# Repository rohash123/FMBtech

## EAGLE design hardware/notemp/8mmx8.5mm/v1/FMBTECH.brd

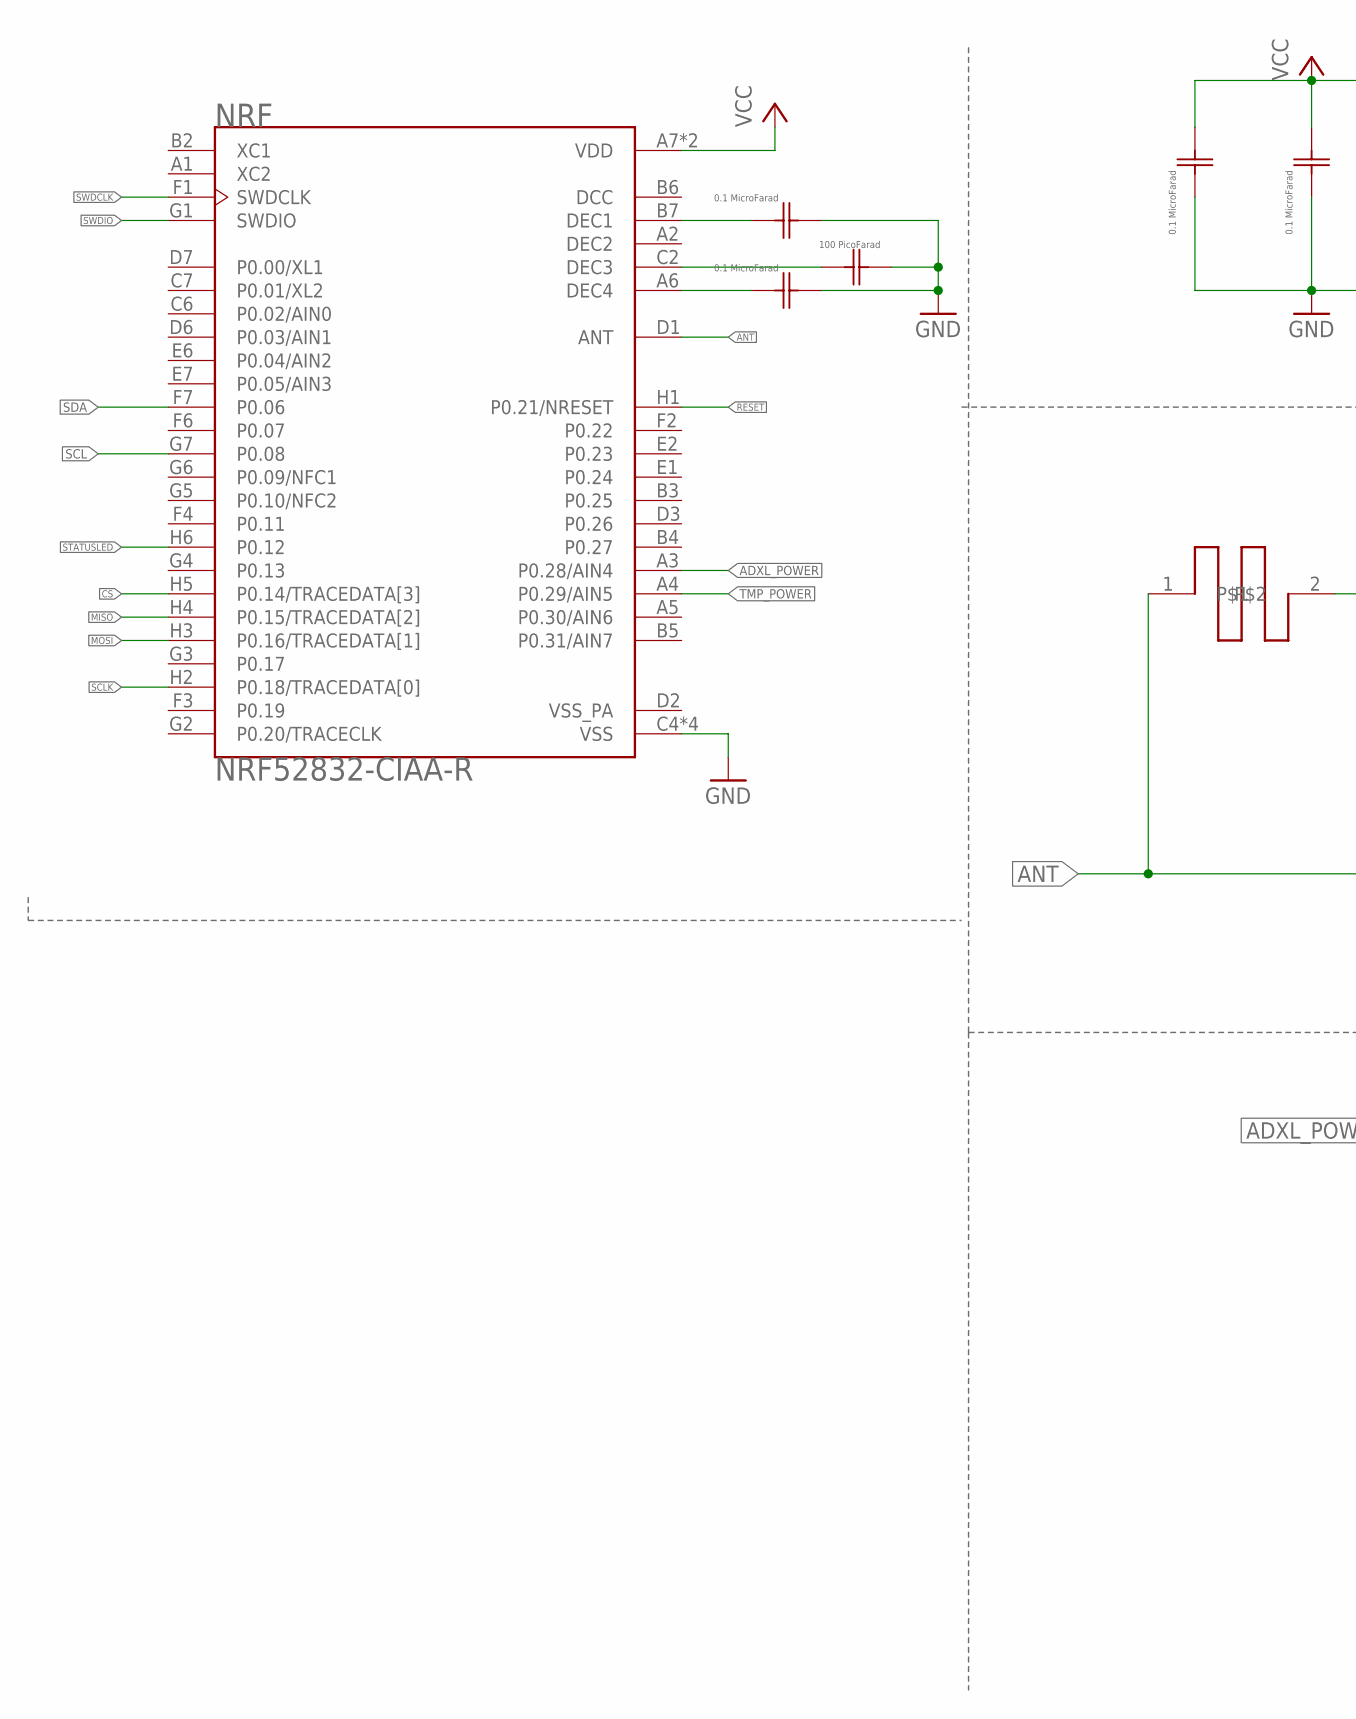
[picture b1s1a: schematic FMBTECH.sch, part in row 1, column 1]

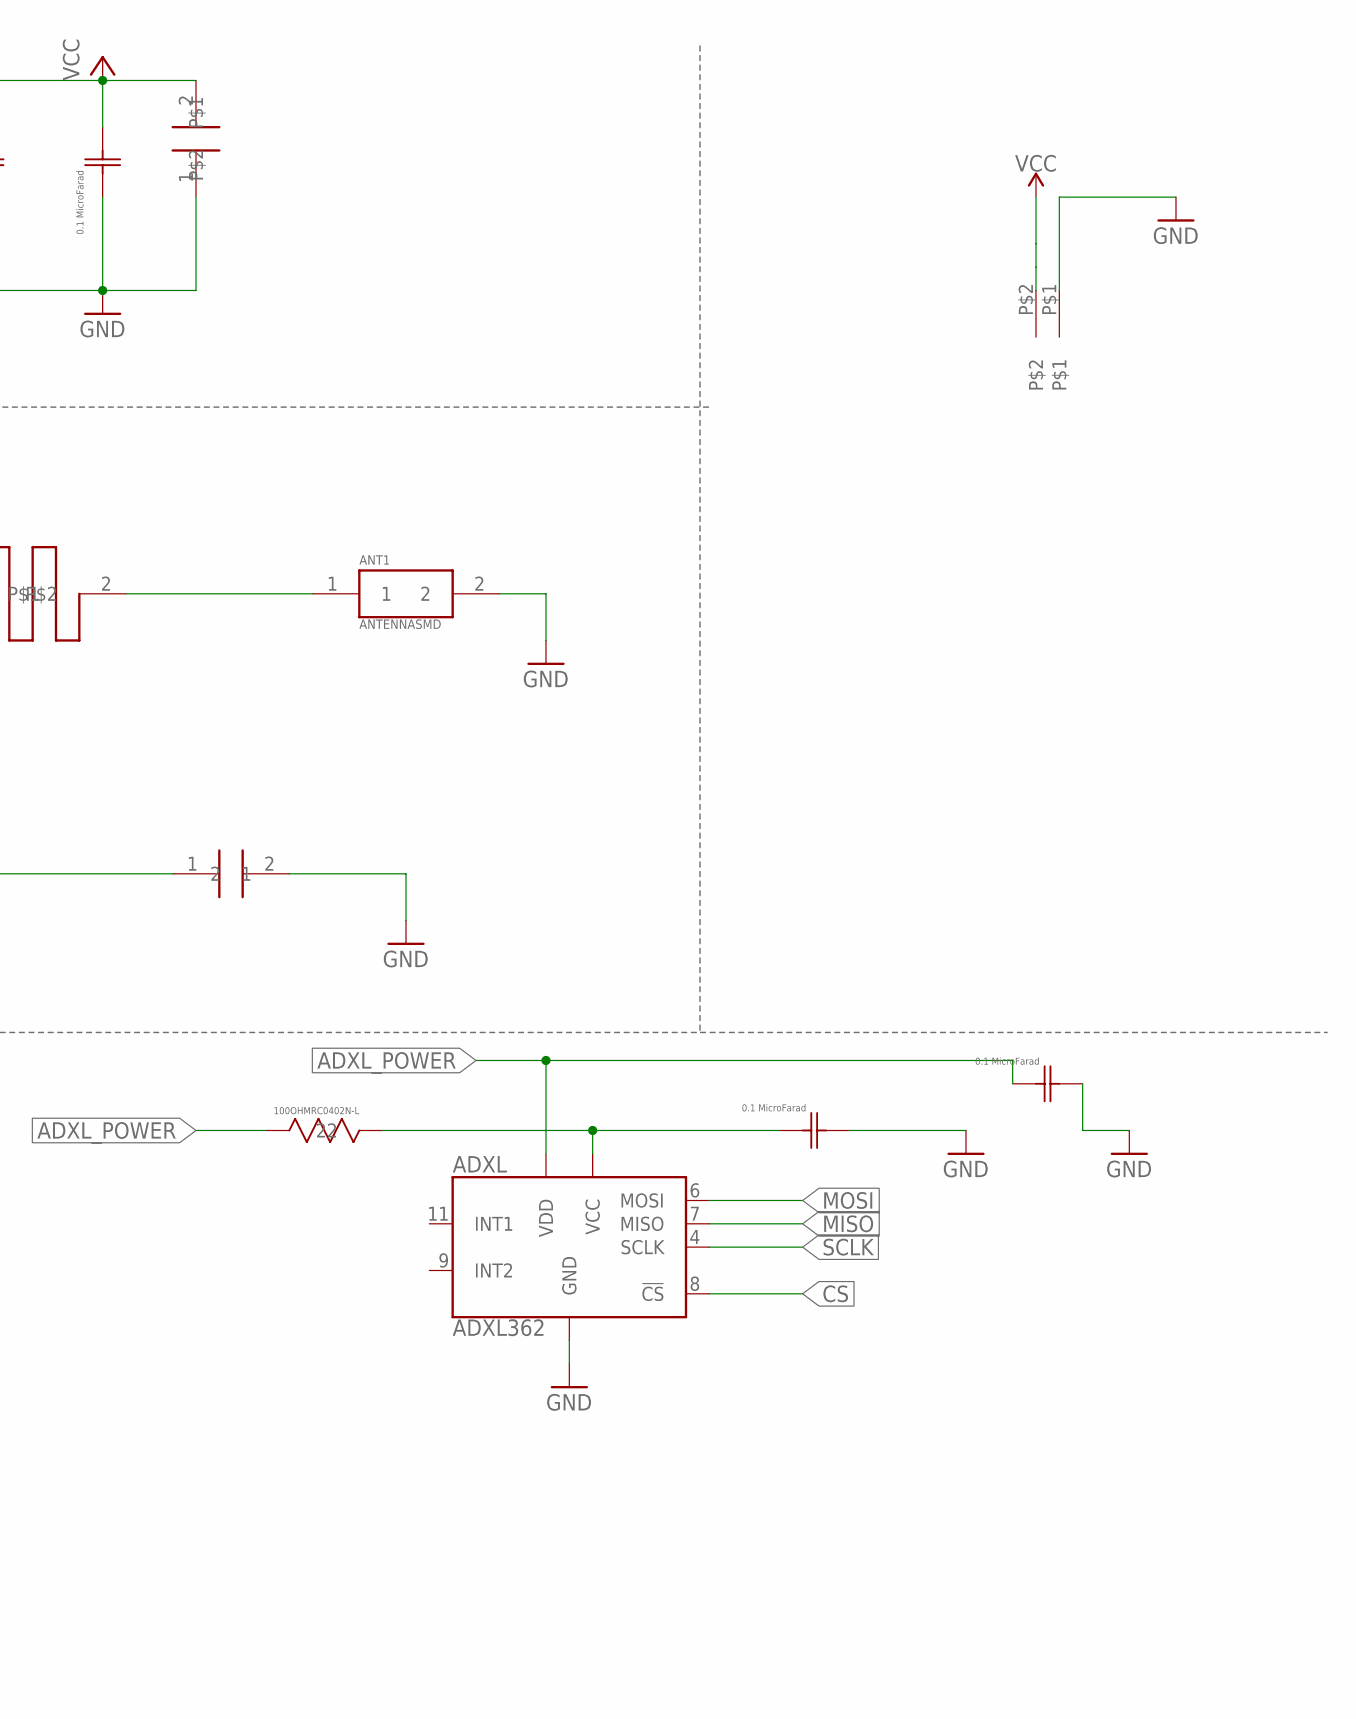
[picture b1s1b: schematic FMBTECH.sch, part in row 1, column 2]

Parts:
ADXL: ADXL362; TFLGA-16/3.3MMX3.1MM
ANT1: ANTENNASMD; 1
C1, C2, C6, C7, C8, C9: 02016D104KAT2A; 0201
C3: GRM0335C1E101JA01D; G-033
NRF: NRF52832-CIAA-R; BGA50N40P7X8_300X320X40
R6: 100OHMRC0402N-L; RES
U$1: 4.7µF; CAP
U$2: 0.8PF; CAP
U$3: INDUCTOR; 1
U$4: SUPPLY

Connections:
ADXL_POWER: ADXL.1 (VDD), C9.1, NRF.A3 (P0.28/AIN4), R6.1 (11)
ANT: NRF.D1 (ANT), U$2.1, U$3.1
CS: ADXL.8 (!CS), NRF.H5 (P0.14/TRACEDATA[3])
DCC: NRF.B6 (DCC)
DEC2: NRF.A2 (DEC2)
GND: ADXL.12 (GND), ADXL.13 (GND), ADXL.16 (GND), ANT1.2, C1.2, C2.2, C3.2 (22), C6.1, C7.1, C8.2, C9.2, NRF.C4 (VSS), NRF.C5 (VSS), NRF.E3 (VSS), NRF.F5 (VSS), U$1.1, U$2.2, U$4.P$1
MISO: ADXL.7 (MISO), NRF.H4 (P0.15/TRACEDATA[2])
MOSI: ADXL.6 (MOSI), NRF.H3 (P0.16/TRACEDATA[1])
unnamed: ANT1.1, U$3.2
unnamed: C2.1, NRF.A6 (DEC4)
unnamed: C1.1, NRF.B7 (DEC1)
unnamed: C3.1 (11), NRF.C2 (DEC3)
unnamed: ADXL.14 (VCC), C8.1, R6.2 (22)
RESET: NRF.H1 (P0.21/NRESET)
SCL: NRF.G7 (P0.08)
SCLK: ADXL.4 (SCLK), NRF.H2 (P0.18/TRACEDATA[0])
SDA: NRF.F7 (P0.06)
STATUSLED: NRF.H6 (P0.12)
SWDCLK: NRF.F1 (SWDCLK)
SWDIO: NRF.G1 (SWDIO)
TMP_POWER: NRF.A4 (P0.29/AIN5)
VCC: C6.2, C7.2, NRF.A7 (VDD), NRF.H7 (VDD), U$1.2, U$4.P$2
VSS_PA: NRF.D2 (VSS_PA)

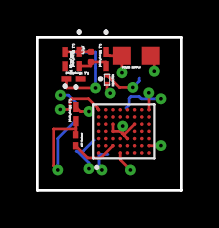
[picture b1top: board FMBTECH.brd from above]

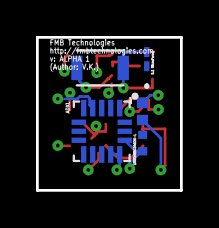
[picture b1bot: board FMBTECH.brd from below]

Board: 6 copper layers, 8.0 x 8.5 mm, 15 parts (5 on the bottom side), 13 nets.

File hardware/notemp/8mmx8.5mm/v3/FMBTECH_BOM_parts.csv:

"Part";"Value";"Device";"Package";"Description";"";
"ADXL";"ADXL362";"ADXL362";"TFLGA-16/3.3MMX3.1MM";"IC ACCEL DIG LO PWR 3AX 16LGA";"";
"ANT1";"ANTENNASMD";"ANTENNASMD";"1";"";"";
"C1";"02016D104KAT2A";"02016D104KAT2A";"0201";"";"";
"C2";"02016D104KAT2A";"02016D104KAT2A";"0201";"";"";
"C3";"GRM0335C1E101JA01D";"GRM0335C1E101JA01D";"G-033";"";"";
"C6";"02016D104KAT2A";"02016D104KAT2A";"0201";"";"";
"C7";"02016D104KAT2A";"02016D104KAT2A";"0201";"";"";
"C8";"02016D104KAT2A";"02016D104KAT2A";"0201";"";"";
"C9";"02016D104KAT2A";"02016D104KAT2A";"0201";"";"";
"NRF";"NRF52832-CIAA-R";"NRF52832-CIAA-R";"BGA50N40P7X8_300X320X40";"Multi Protocal Bluetooth Smart ANT 2.4GHz RF SoC (WL-CSP)";"";
"R6";"100OHMRC0402N-L";"100OHMRC0402N-L";"RES";"";"";
"U$1";"4.7µF";"4.7µF";"CAP";"";"";
"U$2";"0.8PF";"0.8PF";"CAP";"";"";
"U$3";"INDUCTOR";"INDUCTOR";"1";"";"";
"U$4";"SUPPLY";"SUPPLY";"SUPPLY";"";"";

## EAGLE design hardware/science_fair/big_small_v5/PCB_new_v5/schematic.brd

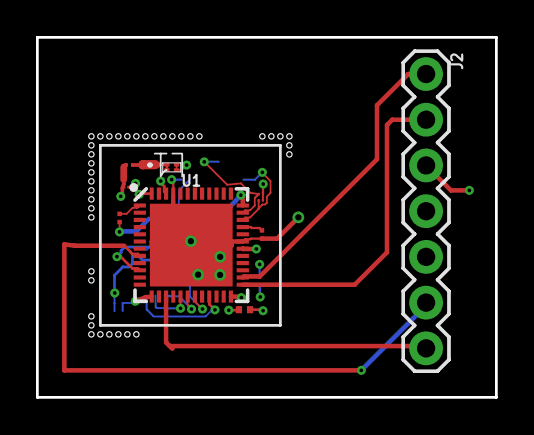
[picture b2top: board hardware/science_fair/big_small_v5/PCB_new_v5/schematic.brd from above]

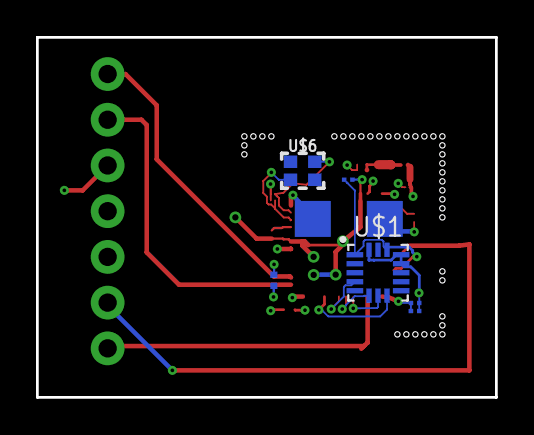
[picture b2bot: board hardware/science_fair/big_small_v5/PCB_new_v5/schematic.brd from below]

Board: 6 copper layers, 25.5 x 20.0 mm, 17 parts (7 on the bottom side), 19 nets.

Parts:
C1, C2, C3, C4: C0402X5R0G104M020BCCAP_0402-L; CAP_0402-L
C5: C0402C0G1C101J020BCCAP_0402-L; CAP_0402-L
J2: header; 1X07
L1: MLG0402Q3N9ST000IND_0402-L; IND_0402-L
U1: NRF52832; QFN48-6X6MM
U$1: ADXL362; TFLGA-16/3.3MMX3.1MM
U$2: 4P7UFCAPACITOR
U$4: 0P8PFCAPACITOR
U$5: ANTENNA; ANTENNA_FOOTPRINT
U$6: 32MHZCRYSTAL
U$7: 1UFCAPACITOR
U$8, U$9: 6PFCAPACITOR
U$10: POWER

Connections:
ADXL_POWER-QFAA: C1.2, U1.10, U$1.VDD/IO, U$1.VS
ANT-QFAA: L1.2, U1.30, U$4.P$2
CS-QFAA: U1.21, U$1.CS
DEC1-QFAA: C2.1, U1.1
DEC3-QFAA: C5.1, U1.33
DEC4-QFAA: U1.46, U$7.P$4
GND: C1.1, C2.2, C3.1, C4.1, C5.2, J2.4, U1.31, U1.45, U1.EP, U$1.GND@1, U$1.GND@2, U$1.GND@3, U$2.P$4, U$4.P$1, U$5.GND@1, U$5.GND@2, U$7.P$3, U$8.P$1, U$9.P$1, U$10.GND
MISO-QFAA: U1.17, U$1.MISO
MOSI-QFAA: U1.18, U$1.MOSI
unnamed: L1.1, U$5.FEED@1, U$5.FEED@2
P0.06-QFAA: J2.6, U1.8
P0.12-QFAA: J2.7, U1.15
RESET-QFAA: J2.5, U1.24
SCLK-QFAA: U1.19, U$1.SCLK
SWDCLK-QFAA: J2.2, U1.25
SWDIO-QFAA: J2.1, U1.26
VDD: C3.2, C4.2, J2.3, U1.13, U1.36, U1.48, U$2.P$3, U$10.VDD
XC1-QFAA: U1.34, U$6.1, U$8.P$2
XC2-QFAA: U1.35, U$6.3, U$9.P$2

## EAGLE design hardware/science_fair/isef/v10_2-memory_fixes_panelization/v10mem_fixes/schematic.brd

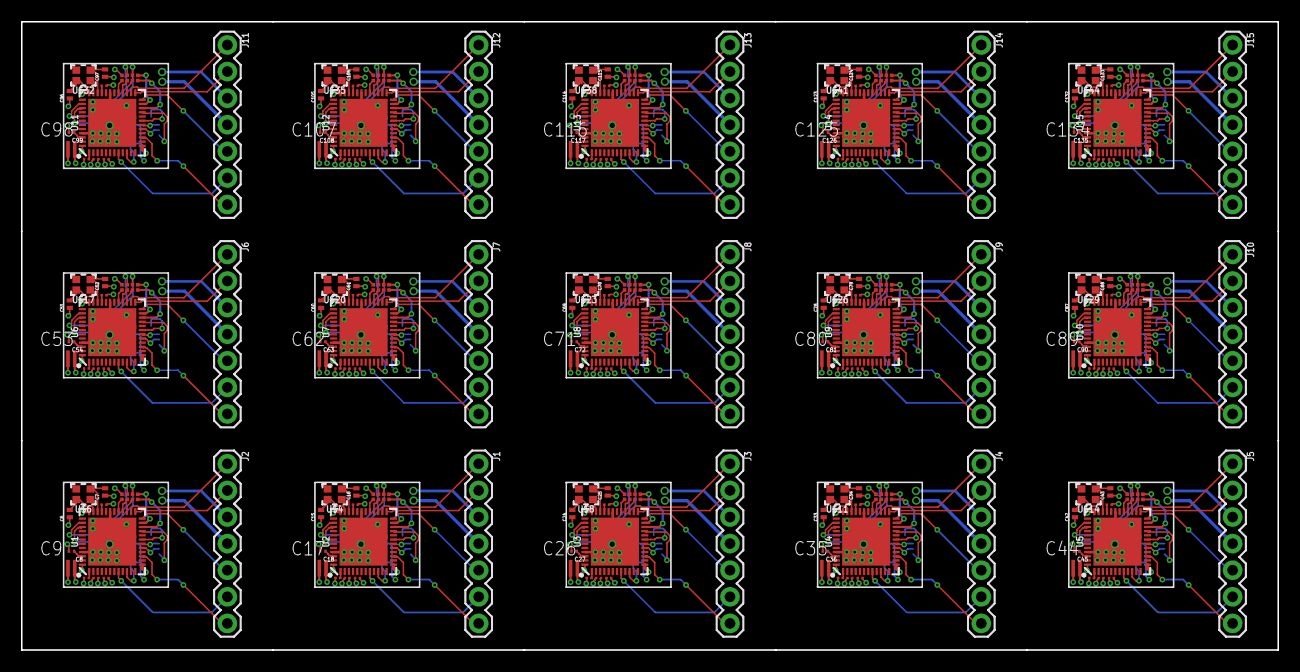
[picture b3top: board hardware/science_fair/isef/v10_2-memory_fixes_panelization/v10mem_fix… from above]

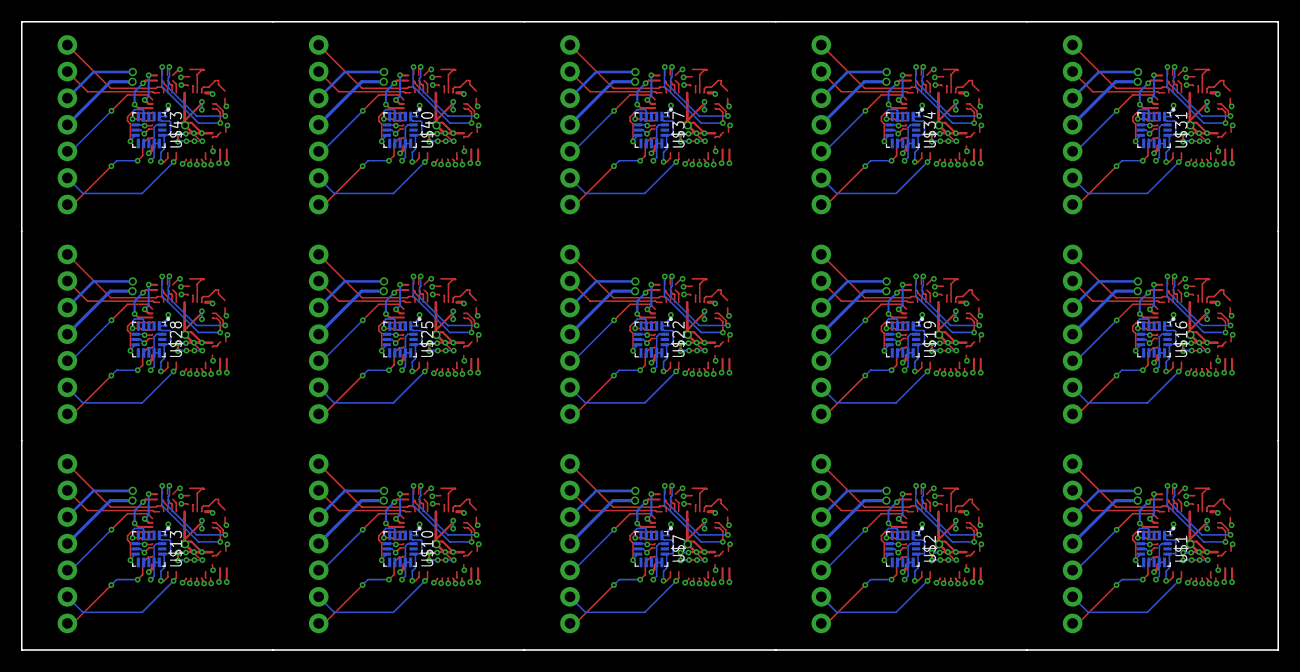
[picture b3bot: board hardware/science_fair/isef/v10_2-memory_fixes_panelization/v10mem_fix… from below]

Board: 4 copper layers, 120.0 x 60.0 mm, 210 parts (30 on the bottom side), 360 nets.

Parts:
C1, C2, C3, C4, C10, C11, C12, C13, C19, C20, C21, C22, C28, C29, C30, C31, C37, C38, C39, C40, C46, C47, C48, C49, C55, C56, C57, C58, C64, C65, C66, C67, C73, C74, C75, C76, C82, C83, C84, C85, C91, C92, C93, C94, C100, C101, C102, C103, C109, C110, C111, C112, C118, C119, C120, C121, C127, C128, C129, C130: C0402X5R0G104M020BCCAP_0402-L; CAP_0402-L
C5, C14, C23, C32, C41, C50, C59, C68, C77, C86, C95, C104, C113, C122, C131: C0402C0G1C101J020BCCAP_0402-L; CAP_0402-L
C6, C7, C15, C16, C24, C25, C33, C34, C42, C43, C51, C52, C60, C61, C69, C70, C78, C79, C87, C88, C96, C97, C105, C106, C114, C115, C123, C124, C132, C133: GRM1555C1H6R0CA01D; CAPC1005X55N
C8, C18, C27, C36, C45, C54, C63, C72, C81, C90, C99, C108, C117, C126, C135: GRMMDXR60J105ME05D; CAPC0502X28N
C9, C17, C26, C35, C44, C53, C62, C71, C80, C89, C98, C107, C116, C125, C134: 4P7UFCAPACITOR4P7UFCAPACITOR; 4P7UFCAPACITOR
J1, J2, J3, J4, J5, J6, J7, J8, J9, J10, J11, J12, J13, J14, J15: header; 1X07
U1, U2, U3, U4, U5, U6, U7, U8, U9, U10, U11, U12, U13, U14, U15: NRF52832; QFN48-6X6MM
U$1, U$2, U$7, U$10, U$13, U$16, U$19, U$22, U$25, U$28, U$31, U$34, U$37, U$40, U$43: ADXL362; TFLGA-16/3.3MMX3.1MM
U$3, U$5, U$9, U$12, U$15, U$18, U$21, U$24, U$27, U$30, U$33, U$36, U$39, U$42, U$45: AT25SF161-UUD-T
U$4, U$6, U$8, U$11, U$14, U$17, U$20, U$23, U$26, U$29, U$32, U$35, U$38, U$41, U$44: 32MHZCRYSTAL

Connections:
ADXL_POWER-QFAA: C1.2, U1.10, U$1.VDD/IO, U$1.VS
ADXL_POWER-QFAA1: C10.2, U2.10, U$2.VDD/IO, U$2.VS
ADXL_POWER-QFAA2: C19.2, U3.10, U$7.VDD/IO, U$7.VS
ADXL_POWER-QFAA3: C28.2, U4.10, U$10.VDD/IO, U$10.VS
ADXL_POWER-QFAA4: C37.2, U5.10, U$13.VDD/IO, U$13.VS
ADXL_POWER-QFAA5: C46.2, U6.10, U$16.VDD/IO, U$16.VS
ADXL_POWER-QFAA6: C55.2, U7.10, U$19.VDD/IO, U$19.VS
ADXL_POWER-QFAA7: C64.2, U8.10, U$22.VDD/IO, U$22.VS
ADXL_POWER-QFAA8: C73.2, U9.10, U$25.VDD/IO, U$25.VS
ADXL_POWER-QFAA9: C82.2, U10.10, U$28.VDD/IO, U$28.VS
ADXL_POWER-QFAA10: C91.2, U11.10, U$31.VDD/IO, U$31.VS
ADXL_POWER-QFAA11: C100.2, U12.10, U$34.VDD/IO, U$34.VS
ADXL_POWER-QFAA12: C109.2, U13.10, U$37.VDD/IO, U$37.VS
ADXL_POWER-QFAA13: C118.2, U14.10, U$40.VDD/IO, U$40.VS
ADXL_POWER-QFAA14: C127.2, U15.10, U$43.VDD/IO, U$43.VS
CS-QFAA: U1.21, U$1.CS
CS-QFAA1: U2.21, U$2.CS
CS-QFAA2: U3.21, U$7.CS
CS-QFAA3: U4.21, U$10.CS
CS-QFAA4: U5.21, U$13.CS
CS-QFAA5: U6.21, U$16.CS
CS-QFAA6: U7.21, U$19.CS
CS-QFAA7: U8.21, U$22.CS
CS-QFAA8: U9.21, U$25.CS
CS-QFAA9: U10.21, U$28.CS
CS-QFAA10: U11.21, U$31.CS
CS-QFAA11: U12.21, U$34.CS
CS-QFAA12: U13.21, U$37.CS
CS-QFAA13: U14.21, U$40.CS
CS-QFAA14: U15.21, U$43.CS
CS_FLASH: U1.23, U$3.5
CS_FLASH1: U2.23, U$5.5
CS_FLASH2: U3.23, U$9.5
CS_FLASH3: U4.23, U$12.5
CS_FLASH4: U5.23, U$15.5
CS_FLASH5: U6.23, U$18.5
CS_FLASH6: U7.23, U$21.5
CS_FLASH7: U8.23, U$24.5
CS_FLASH8: U9.23, U$27.5
CS_FLASH9: U10.23, U$30.5
CS_FLASH10: U11.23, U$33.5
CS_FLASH11: U12.23, U$36.5
CS_FLASH12: U13.23, U$39.5
CS_FLASH13: U14.23, U$42.5
CS_FLASH14: U15.23, U$45.5
DEC1-QFAA: C2.1, U1.1
DEC1-QFAA1: C11.1, U2.1
DEC1-QFAA2: C20.1, U3.1
DEC1-QFAA3: C29.1, U4.1
DEC1-QFAA4: C38.1, U5.1
DEC1-QFAA5: C47.1, U6.1
DEC1-QFAA6: C56.1, U7.1
DEC1-QFAA7: C65.1, U8.1
DEC1-QFAA8: C74.1, U9.1
DEC1-QFAA9: C83.1, U10.1
DEC1-QFAA10: C92.1, U11.1
DEC1-QFAA11: C101.1, U12.1
DEC1-QFAA12: C110.1, U13.1
DEC1-QFAA13: C119.1, U14.1
DEC1-QFAA14: C128.1, U15.1
DEC3-QFAA: C5.1, U1.33
DEC3-QFAA1: C14.1, U2.33
DEC3-QFAA2: C23.1, U3.33
DEC3-QFAA3: C32.1, U4.33
DEC3-QFAA4: C41.1, U5.33
DEC3-QFAA5: C50.1, U6.33
DEC3-QFAA6: C59.1, U7.33
DEC3-QFAA7: C68.1, U8.33
DEC3-QFAA8: C77.1, U9.33
DEC3-QFAA9: C86.1, U10.33
DEC3-QFAA10: C95.1, U11.33
DEC3-QFAA11: C104.1, U12.33
DEC3-QFAA12: C113.1, U13.33
DEC3-QFAA13: C122.1, U14.33
DEC3-QFAA14: C131.1, U15.33
DEC4-QFAA: C8.1, U1.46
DEC4-QFAA1: C18.1, U2.46
DEC4-QFAA2: C27.1, U3.46
DEC4-QFAA3: C36.1, U4.46
DEC4-QFAA4: C45.1, U5.46
DEC4-QFAA5: C54.1, U6.46
DEC4-QFAA6: C63.1, U7.46
DEC4-QFAA7: C72.1, U8.46
DEC4-QFAA8: C81.1, U9.46
DEC4-QFAA9: C90.1, U10.46
DEC4-QFAA10: C99.1, U11.46
DEC4-QFAA11: C108.1, U12.46
DEC4-QFAA12: C117.1, U13.46
DEC4-QFAA13: C126.1, U14.46
DEC4-QFAA14: C135.1, U15.46
FLASH_POWER: U1.22, U$3.1
FLASH_POWER1: U2.22, U$5.1
FLASH_POWER2: U3.22, U$9.1
FLASH_POWER3: U4.22, U$12.1
FLASH_POWER4: U5.22, U$15.1
FLASH_POWER5: U6.22, U$18.1
FLASH_POWER6: U7.22, U$21.1
FLASH_POWER7: U8.22, U$24.1
FLASH_POWER8: U9.22, U$27.1
FLASH_POWER9: U10.22, U$30.1
FLASH_POWER10: U11.22, U$33.1
FLASH_POWER11: U12.22, U$36.1
FLASH_POWER12: U13.22, U$39.1
FLASH_POWER13: U14.22, U$42.1
FLASH_POWER14: U15.22, U$45.1
GND: C1.1, C2.2, C3.1, C4.1, C5.2, C6.1, C7.1, C8.2, C9.1, J2.4, U1.31, U1.45, U1.EP, U$1.GND@1, U$1.GND@2, U$1.GND@3, U$3.8
GND1: C10.1, C11.2, C12.1, C13.1, C14.2, C15.1, C16.1, C17.1, C18.2, J1.4, U2.31, U2.45, U2.EP, U$2.GND@1, U$2.GND@2, U$2.GND@3, U$5.8
GND2: C19.1, C20.2, C21.1, C22.1, C23.2, C24.1, C25.1, C26.1, C27.2, J3.4, U3.31, U3.45, U3.EP, U$7.GND@1, U$7.GND@2, U$7.GND@3, U$9.8
GND3: C28.1, C29.2, C30.1, C31.1, C32.2, C33.1, C34.1, C35.1, C36.2, J4.4, U4.31, U4.45, U4.EP, U$10.GND@1, U$10.GND@2, U$10.GND@3, U$12.8
GND4: C37.1, C38.2, C39.1, C40.1, C41.2, C42.1, C43.1, C44.1, C45.2, J5.4, U5.31, U5.45, U5.EP, U$13.GND@1, U$13.GND@2, U$13.GND@3, U$15.8
GND5: C46.1, C47.2, C48.1, C49.1, C50.2, C51.1, C52.1, C53.1, C54.2, J6.4, U6.31, U6.45, U6.EP, U$16.GND@1, U$16.GND@2, U$16.GND@3, U$18.8
GND6: C55.1, C56.2, C57.1, C58.1, C59.2, C60.1, C61.1, C62.1, C63.2, J7.4, U7.31, U7.45, U7.EP, U$19.GND@1, U$19.GND@2, U$19.GND@3, U$21.8
GND7: C64.1, C65.2, C66.1, C67.1, C68.2, C69.1, C70.1, C71.1, C72.2, J8.4, U8.31, U8.45, U8.EP, U$22.GND@1, U$22.GND@2, U$22.GND@3, U$24.8
GND8: C73.1, C74.2, C75.1, C76.1, C77.2, C78.1, C79.1, C80.1, C81.2, J9.4, U9.31, U9.45, U9.EP, U$25.GND@1, U$25.GND@2, U$25.GND@3, U$27.8
GND9: C82.1, C83.2, C84.1, C85.1, C86.2, C87.1, C88.1, C89.1, C90.2, J10.4, U10.31, U10.45, U10.EP, U$28.GND@1, U$28.GND@2, U$28.GND@3, U$30.8
GND10: C91.1, C92.2, C93.1, C94.1, C95.2, C96.1, C97.1, C98.1, C99.2, J11.4, U11.31, U11.45, U11.EP, U$31.GND@1, U$31.GND@2, U$31.GND@3, U$33.8
GND11: C100.1, C101.2, C102.1, C103.1, C104.2, C105.1, C106.1, C107.1, C108.2, J12.4, U12.31, U12.45, U12.EP, U$34.GND@1, U$34.GND@2, U$34.GND@3, U$36.8
GND12: C109.1, C110.2, C111.1, C112.1, C113.2, C114.1, C115.1, C116.1, C117.2, J13.4, U13.31, U13.45, U13.EP, U$37.GND@1, U$37.GND@2, U$37.GND@3, U$39.8
GND13: C118.1, C119.2, C120.1, C121.1, C122.2, C123.1, C124.1, C125.1, C126.2, J14.4, U14.31, U14.45, U14.EP, U$40.GND@1, U$40.GND@2, U$40.GND@3, U$42.8
GND14: C127.1, C128.2, C129.1, C130.1, C131.2, C132.1, C133.1, C134.1, C135.2, J15.4, U15.31, U15.45, U15.EP, U$43.GND@1, U$43.GND@2, U$43.GND@3, U$45.8
HOLD_FLASH: U1.27, U$3.2
HOLD_FLASH1: U2.27, U$5.2
HOLD_FLASH2: U3.27, U$9.2
HOLD_FLASH3: U4.27, U$12.2
HOLD_FLASH4: U5.27, U$15.2
HOLD_FLASH5: U6.27, U$18.2
HOLD_FLASH6: U7.27, U$21.2
HOLD_FLASH7: U8.27, U$24.2
HOLD_FLASH8: U9.27, U$27.2
HOLD_FLASH9: U10.27, U$30.2
HOLD_FLASH10: U11.27, U$33.2
HOLD_FLASH11: U12.27, U$36.2
HOLD_FLASH12: U13.27, U$39.2
HOLD_FLASH13: U14.27, U$42.2
HOLD_FLASH14: U15.27, U$45.2
MISO-QFAA: U1.17, U$1.MISO
MISO-QFAA1: U2.17, U$2.MISO
MISO-QFAA2: U3.17, U$7.MISO
MISO-QFAA3: U4.17, U$10.MISO
MISO-QFAA4: U5.17, U$13.MISO
MISO-QFAA5: U6.17, U$16.MISO
MISO-QFAA6: U7.17, U$19.MISO
MISO-QFAA7: U8.17, U$22.MISO
MISO-QFAA8: U9.17, U$25.MISO
MISO-QFAA9: U10.17, U$28.MISO
MISO-QFAA10: U11.17, U$31.MISO
MISO-QFAA11: U12.17, U$34.MISO
MISO-QFAA12: U13.17, U$37.MISO
MISO-QFAA13: U14.17, U$40.MISO
MISO-QFAA14: U15.17, U$43.MISO
MOSI-QFAA: U1.18, U$1.MOSI
MOSI-QFAA1: U2.18, U$2.MOSI
MOSI-QFAA2: U3.18, U$7.MOSI
MOSI-QFAA3: U4.18, U$10.MOSI
MOSI-QFAA4: U5.18, U$13.MOSI
MOSI-QFAA5: U6.18, U$16.MOSI
MOSI-QFAA6: U7.18, U$19.MOSI
MOSI-QFAA7: U8.18, U$22.MOSI
MOSI-QFAA8: U9.18, U$25.MOSI
MOSI-QFAA9: U10.18, U$28.MOSI
MOSI-QFAA10: U11.18, U$31.MOSI
MOSI-QFAA11: U12.18, U$34.MOSI
MOSI-QFAA12: U13.18, U$37.MOSI
MOSI-QFAA13: U14.18, U$40.MOSI
MOSI-QFAA14: U15.18, U$43.MOSI
P0.06-QFAA: J2.6, U1.8
P0.06-QFAA1: J1.6, U2.8
P0.06-QFAA2: J3.6, U3.8
P0.06-QFAA3: J4.6, U4.8
P0.06-QFAA4: J5.6, U5.8
P0.06-QFAA5: J6.6, U6.8
P0.06-QFAA6: J7.6, U7.8
P0.06-QFAA7: J8.6, U8.8
P0.06-QFAA8: J9.6, U9.8
P0.06-QFAA9: J10.6, U10.8
P0.06-QFAA10: J11.6, U11.8
P0.06-QFAA11: J12.6, U12.8
P0.06-QFAA12: J13.6, U13.8
P0.06-QFAA13: J14.6, U14.8
P0.06-QFAA14: J15.6, U15.8
P0.12-QFAA: J2.7, U1.15
P0.12-QFAA1: J1.7, U2.15
P0.12-QFAA2: J3.7, U3.15
P0.12-QFAA3: J4.7, U4.15
P0.12-QFAA4: J5.7, U5.15
P0.12-QFAA5: J6.7, U6.15
P0.12-QFAA6: J7.7, U7.15
P0.12-QFAA7: J8.7, U8.15
P0.12-QFAA8: J9.7, U9.15
P0.12-QFAA9: J10.7, U10.15
P0.12-QFAA10: J11.7, U11.15
P0.12-QFAA11: J12.7, U12.15
P0.12-QFAA12: J13.7, U13.15
P0.12-QFAA13: J14.7, U14.15
P0.12-QFAA14: J15.7, U15.15
RESET-QFAA: J2.5, U1.24
RESET-QFAA1: J1.5, U2.24
RESET-QFAA2: J3.5, U3.24
RESET-QFAA3: J4.5, U4.24
RESET-QFAA4: J5.5, U5.24
RESET-QFAA5: J6.5, U6.24
RESET-QFAA6: J7.5, U7.24
RESET-QFAA7: J8.5, U8.24
RESET-QFAA8: J9.5, U9.24
RESET-QFAA9: J10.5, U10.24
RESET-QFAA10: J11.5, U11.24
RESET-QFAA11: J12.5, U12.24
RESET-QFAA12: J13.5, U13.24
RESET-QFAA13: J14.5, U14.24
RESET-QFAA14: J15.5, U15.24
SCK_FLASH: U1.28, U$3.3
SCK_FLASH1: U2.28, U$5.3
SCK_FLASH2: U3.28, U$9.3
SCK_FLASH3: U4.28, U$12.3
SCK_FLASH4: U5.28, U$15.3
SCK_FLASH5: U6.28, U$18.3
SCK_FLASH6: U7.28, U$21.3
SCK_FLASH7: U8.28, U$24.3
SCK_FLASH8: U9.28, U$27.3
SCK_FLASH9: U10.28, U$30.3
SCK_FLASH10: U11.28, U$33.3
SCK_FLASH11: U12.28, U$36.3
SCK_FLASH12: U13.28, U$39.3
SCK_FLASH13: U14.28, U$42.3
SCK_FLASH14: U15.28, U$45.3
SCLK-QFAA: U1.19, U$1.SCLK
SCLK-QFAA1: U2.19, U$2.SCLK
SCLK-QFAA2: U3.19, U$7.SCLK
SCLK-QFAA3: U4.19, U$10.SCLK
SCLK-QFAA4: U5.19, U$13.SCLK
SCLK-QFAA5: U6.19, U$16.SCLK
SCLK-QFAA6: U7.19, U$19.SCLK
SCLK-QFAA7: U8.19, U$22.SCLK
SCLK-QFAA8: U9.19, U$25.SCLK
SCLK-QFAA9: U10.19, U$28.SCLK
SCLK-QFAA10: U11.19, U$31.SCLK
SCLK-QFAA11: U12.19, U$34.SCLK
SCLK-QFAA12: U13.19, U$37.SCLK
SCLK-QFAA13: U14.19, U$40.SCLK
SCLK-QFAA14: U15.19, U$43.SCLK
SI_FLASH: U1.29, U$3.4
SI_FLASH1: U2.29, U$5.4
SI_FLASH2: U3.29, U$9.4
SI_FLASH3: U4.29, U$12.4
SI_FLASH4: U5.29, U$15.4
SI_FLASH5: U6.29, U$18.4
SI_FLASH6: U7.29, U$21.4
SI_FLASH7: U8.29, U$24.4
SI_FLASH8: U9.29, U$27.4
SI_FLASH9: U10.29, U$30.4
SI_FLASH10: U11.29, U$33.4
SI_FLASH11: U12.29, U$36.4
SI_FLASH12: U13.29, U$39.4
SI_FLASH13: U14.29, U$42.4
SI_FLASH14: U15.29, U$45.4
SO_FLASH: U1.39, U$3.6
SO_FLASH1: U2.39, U$5.6
SO_FLASH2: U3.39, U$9.6
SO_FLASH3: U4.39, U$12.6
SO_FLASH4: U5.39, U$15.6
SO_FLASH5: U6.39, U$18.6
SO_FLASH6: U7.39, U$21.6
SO_FLASH7: U8.39, U$24.6
SO_FLASH8: U9.39, U$27.6
SO_FLASH9: U10.39, U$30.6
SO_FLASH10: U11.39, U$33.6
SO_FLASH11: U12.39, U$36.6
SO_FLASH12: U13.39, U$39.6
SO_FLASH13: U14.39, U$42.6
SO_FLASH14: U15.39, U$45.6
SWDCLK-QFAA: J2.2, U1.25
SWDCLK-QFAA1: J1.2, U2.25
SWDCLK-QFAA2: J3.2, U3.25
SWDCLK-QFAA3: J4.2, U4.25
SWDCLK-QFAA4: J5.2, U5.25
SWDCLK-QFAA5: J6.2, U6.25
SWDCLK-QFAA6: J7.2, U7.25
SWDCLK-QFAA7: J8.2, U8.25
SWDCLK-QFAA8: J9.2, U9.25
SWDCLK-QFAA9: J10.2, U10.25
SWDCLK-QFAA10: J11.2, U11.25
SWDCLK-QFAA11: J12.2, U12.25
SWDCLK-QFAA12: J13.2, U13.25
SWDCLK-QFAA13: J14.2, U14.25
SWDCLK-QFAA14: J15.2, U15.25
SWDIO-QFAA: J2.1, U1.26
SWDIO-QFAA1: J1.1, U2.26
SWDIO-QFAA2: J3.1, U3.26
SWDIO-QFAA3: J4.1, U4.26
SWDIO-QFAA4: J5.1, U5.26
SWDIO-QFAA5: J6.1, U6.26
SWDIO-QFAA6: J7.1, U7.26
SWDIO-QFAA7: J8.1, U8.26
SWDIO-QFAA8: J9.1, U9.26
SWDIO-QFAA9: J10.1, U10.26
SWDIO-QFAA10: J11.1, U11.26
SWDIO-QFAA11: J12.1, U12.26
SWDIO-QFAA12: J13.1, U13.26
SWDIO-QFAA13: J14.1, U14.26
SWDIO-QFAA14: J15.1, U15.26
VDD: C3.2, C4.2, C9.2, J2.3, U1.13, U1.36, U1.48
VDD1: C12.2, C13.2, C17.2, J1.3, U2.13, U2.36, U2.48
VDD2: C21.2, C22.2, C26.2, J3.3, U3.13, U3.36, U3.48
VDD3: C30.2, C31.2, C35.2, J4.3, U4.13, U4.36, U4.48
VDD4: C39.2, C40.2, C44.2, J5.3, U5.13, U5.36, U5.48
VDD5: C48.2, C49.2, C53.2, J6.3, U6.13, U6.36, U6.48
VDD6: C57.2, C58.2, C62.2, J7.3, U7.13, U7.36, U7.48
VDD7: C66.2, C67.2, C71.2, J8.3, U8.13, U8.36, U8.48
VDD8: C75.2, C76.2, C80.2, J9.3, U9.13, U9.36, U9.48
VDD9: C84.2, C85.2, C89.2, J10.3, U10.13, U10.36, U10.48
VDD10: C93.2, C94.2, C98.2, J11.3, U11.13, U11.36, U11.48
VDD11: C102.2, C103.2, C107.2, J12.3, U12.13, U12.36, U12.48
VDD12: C111.2, C112.2, C116.2, J13.3, U13.13, U13.36, U13.48
VDD13: C120.2, C121.2, C125.2, J14.3, U14.13, U14.36, U14.48
VDD14: C129.2, C130.2, C134.2, J15.3, U15.13, U15.36, U15.48
WP_FLASH: U1.38, U$3.7
WP_FLASH1: U2.38, U$5.7
WP_FLASH2: U3.38, U$9.7
WP_FLASH3: U4.38, U$12.7
WP_FLASH4: U5.38, U$15.7
WP_FLASH5: U6.38, U$18.7
WP_FLASH6: U7.38, U$21.7
WP_FLASH7: U8.38, U$24.7
WP_FLASH8: U9.38, U$27.7
WP_FLASH9: U10.38, U$30.7
WP_FLASH10: U11.38, U$33.7
WP_FLASH11: U12.38, U$36.7
WP_FLASH12: U13.38, U$39.7
WP_FLASH13: U14.38, U$42.7
WP_FLASH14: U15.38, U$45.7
XC1-QFAA: C7.2, U1.34, U$6.1
XC1-QFAA1: C16.2, U2.34, U$4.1
XC1-QFAA2: C25.2, U3.34, U$8.1
XC1-QFAA3: C34.2, U4.34, U$11.1
XC1-QFAA4: C43.2, U5.34, U$14.1
XC1-QFAA5: C52.2, U6.34, U$17.1
XC1-QFAA6: C61.2, U7.34, U$20.1
XC1-QFAA7: C70.2, U8.34, U$23.1
XC1-QFAA8: C79.2, U9.34, U$26.1
XC1-QFAA9: C88.2, U10.34, U$29.1
XC1-QFAA10: C97.2, U11.34, U$32.1
XC1-QFAA11: C106.2, U12.34, U$35.1
XC1-QFAA12: C115.2, U13.34, U$38.1
XC1-QFAA13: C124.2, U14.34, U$41.1
XC1-QFAA14: C133.2, U15.34, U$44.1
XC2-QFAA: C6.2, U1.35, U$6.3
XC2-QFAA1: C15.2, U2.35, U$4.3
XC2-QFAA2: C24.2, U3.35, U$8.3
XC2-QFAA3: C33.2, U4.35, U$11.3
XC2-QFAA4: C42.2, U5.35, U$14.3
XC2-QFAA5: C51.2, U6.35, U$17.3
XC2-QFAA6: C60.2, U7.35, U$20.3
XC2-QFAA7: C69.2, U8.35, U$23.3
XC2-QFAA8: C78.2, U9.35, U$26.3
XC2-QFAA9: C87.2, U10.35, U$29.3
XC2-QFAA10: C96.2, U11.35, U$32.3
XC2-QFAA11: C105.2, U12.35, U$35.3
XC2-QFAA12: C114.2, U13.35, U$38.3
XC2-QFAA13: C123.2, U14.35, U$41.3
XC2-QFAA14: C132.2, U15.35, U$44.3

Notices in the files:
parts and their libraries:
SparkFun-Aesthetics: Licensing: Creative Commons ShareAlike 4.0 International - https://creativecommons.org/licenses/by-sa/4.0
